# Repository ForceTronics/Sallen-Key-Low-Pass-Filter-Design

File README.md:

# Sallen-Key-Low-Pass-Filter-Design
This is from a video tutorial on designing a low pass filter circuit. The video tutorial series can be found on the ForceTronics YouTube Channel

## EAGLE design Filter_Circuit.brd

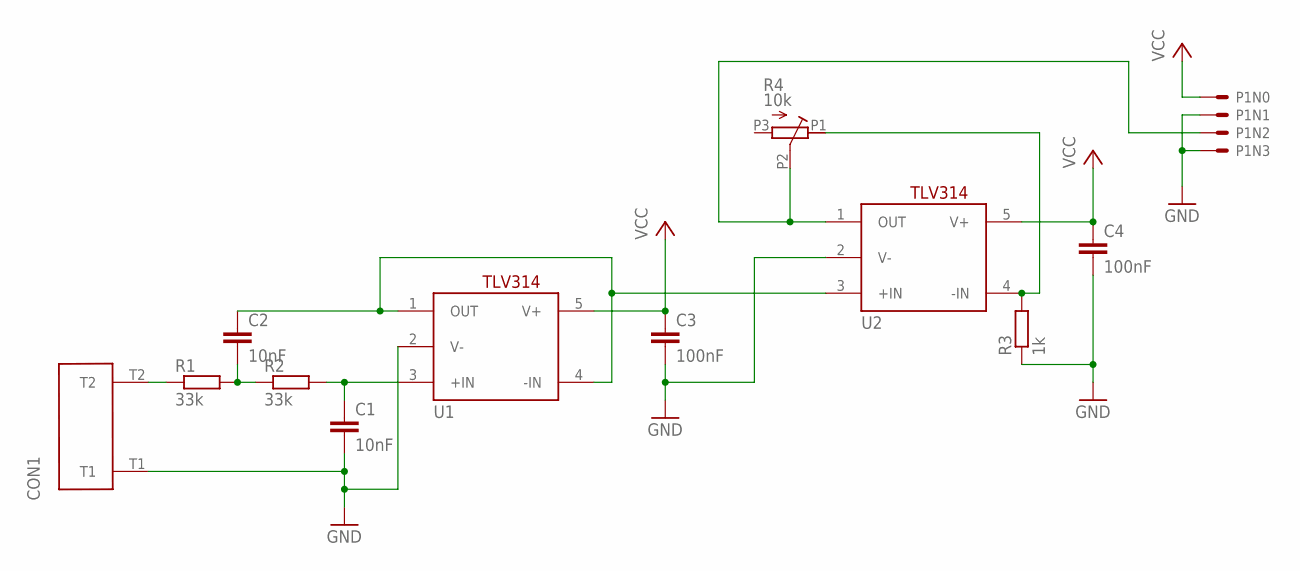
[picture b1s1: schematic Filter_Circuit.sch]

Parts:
C1, C2: 10nF; C1206
C3, C4: 100nF; C1206
CON1: 2PIN_SCREW_TERM
P1: 4PINHEADER
R1, R2: 33k; R1206
R3: 1k; R1206
R4: 10k; POT_RESISTOR_SMD
U1, U2: TLV314_OP_AMP; SOT23

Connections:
GND: C1.2, C3.2, C4.2, CON1.T1, P1.N1, P1.N3, R3.1, U1.2 (V-), U2.2 (V-)
unnamed: CON1.T2, R1.1
unnamed: C2.2, R1.2, R2.1
unnamed: C1.1, R2.2, U1.3 (+IN)
unnamed: C2.1, U1.1 (OUT), U1.4 (-IN), U2.3 (+IN)
unnamed: R3.2, R4.P1, U2.4 (-IN)
unnamed: P1.N2, R4.P2, U2.1 (OUT)
VCC: C3.1, C4.1, P1.N0, U1.5 (V+), U2.5 (V+)

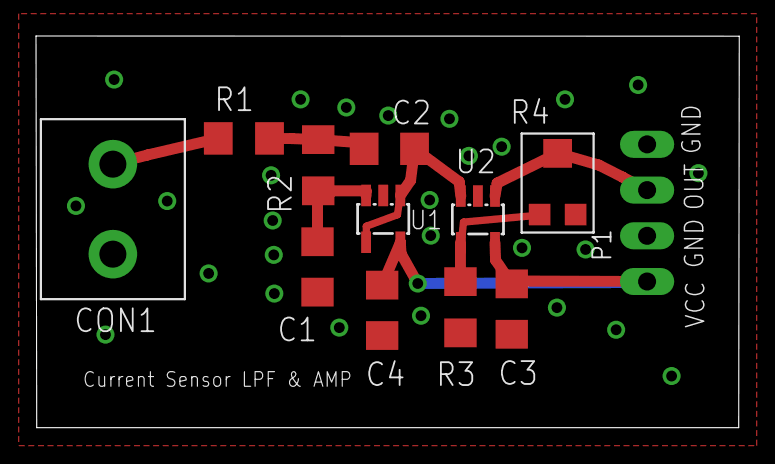
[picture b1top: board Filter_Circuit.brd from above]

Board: 2 copper layers, 39.1 x 21.8 mm, 12 parts (0 on the bottom side), 8 nets.

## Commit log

2017-02-28 Create LPF_Active_Salen_Key.asc
    This is an LTspice file of the Sallen-Key low pass filter design.
2017-03-05 Create Filter_Circuit.sch
    Eagle schematic file for Sallen-Key LPF and amplifier circuit
2017-03-05 Create Filter_Circuit.brd
    Eagle board file for Sallen-Key and amplifier circuit
